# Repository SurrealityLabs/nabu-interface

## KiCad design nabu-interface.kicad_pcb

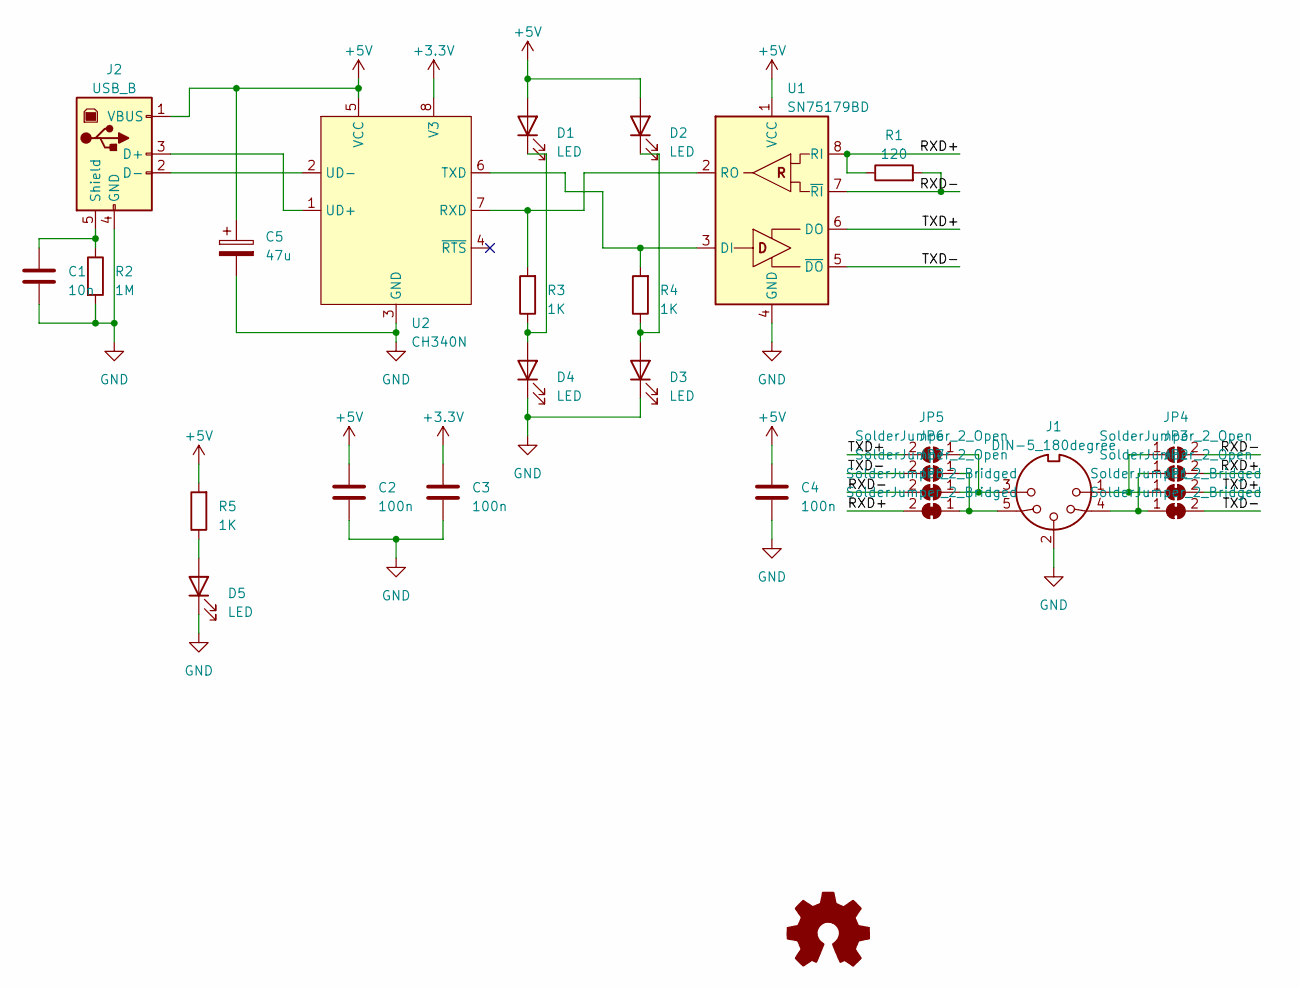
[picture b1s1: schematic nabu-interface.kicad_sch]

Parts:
C1: 10n; C_0603_1608Metric_Pad1.08x0.95mm_HandSolder
C2, C3, C4: 100n; C_0603_1608Metric_Pad1.08x0.95mm_HandSolder
C5: 47u; CP_Radial_D4.0mm_P2.00mm
D1, D2, D3, D4, D5: LED; LED_0603_1608Metric_Pad1.05x0.95mm_HandSolder
J1: DIN-5_180degree; MIDI_DIN5
J2: USB_B; USB_B_OST_USB-B1HSxx_Horizontal
JP1, JP2, JP7, JP8: SolderJumper_2_Bridged; SolderJumper-2_P1.3mm_Bridged_RoundedPad1.0x1.5mm
JP3, JP4, JP5, JP6: SolderJumper_2_Open; SolderJumper-2_P1.3mm_Open_RoundedPad1.0x1.5mm
R1: 120; R_0603_1608Metric_Pad0.98x0.95mm_HandSolder
R2: 1M; R_0603_1608Metric_Pad0.98x0.95mm_HandSolder
R3, R4, R5: 1K; R_0603_1608Metric_Pad0.98x0.95mm_HandSolder
U1: SN75179BD; SOIC-8_3.9x4.9mm_P1.27mm
U2: CH340N; SOP-8_3.9x4.9mm_P1.27mm

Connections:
+3.3V: C3.1, U2.8 (V3)
+5V: C2.1, C4.1, C5.1, D1.2 (A), D2.2 (A), J2.1 (VBUS), R5.2, U1.1 (VCC), U2.5 (VCC)
/RXD+: JP3.2 (B), JP8.2 (B), R1.1, U1.8 (RI)
/RXD-: JP4.2 (B), JP7.2 (B), R1.2, U1.7 (~RI)
/TXD+: JP2.2 (B), JP5.2 (B), U1.6 (DO)
/TXD-: JP1.2 (B), JP6.2 (B), U1.5 (~DO)
GND: C1.2, C2.2, C3.2, C4.2, C5.2, D3.1 (K), D4.1 (K), D5.1 (K), J1.2, J2.4 (GND), R2.2, U1.4 (GND), U2.3 (GND)
unnamed: D1.1 (K), D4.2 (A), R3.1
unnamed: D2.1 (K), D3.2 (A), R4.1
unnamed: D5.2 (A), R5.1
unnamed: J2.3 (D+), U2.1 (UD+)
unnamed: J2.2 (D-), U2.2 (UD-)
unnamed: C1.1, J2.5 (Shield), R2.1
unnamed: J1.4, JP1.1 (A), JP3.1 (A)
unnamed: J1.1, JP2.1 (A), JP4.1 (A)
unnamed: J1.3, JP5.1 (A), JP7.1 (A)
unnamed: J1.5, JP6.1 (A), JP8.1 (A)
unnamed: R4.2, U1.3 (DI), U2.6 (TXD)
unnamed: R3.2, U1.2 (RO), U2.7 (RXD)

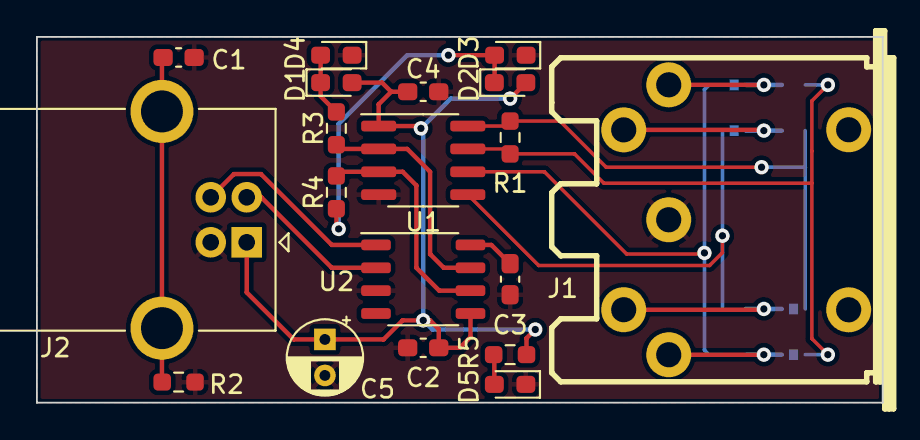
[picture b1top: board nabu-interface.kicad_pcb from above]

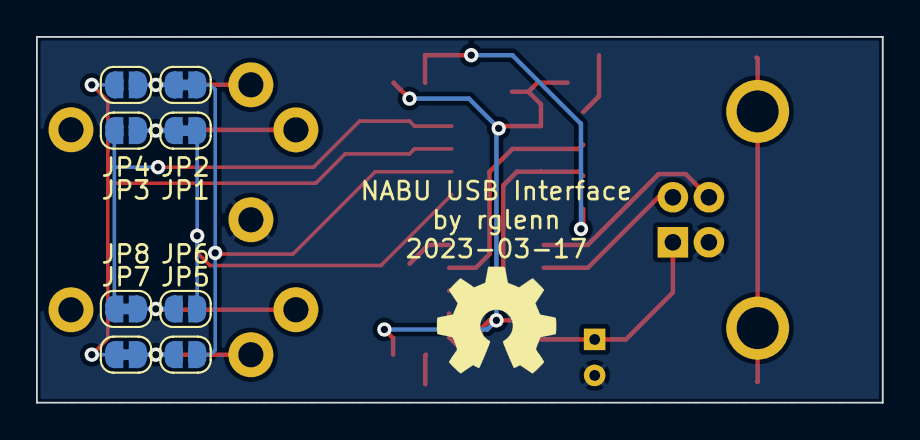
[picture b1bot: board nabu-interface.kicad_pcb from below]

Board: 2 copper layers, 47.0 x 20.3 mm, 27 parts (8 on the bottom side), 19 nets.

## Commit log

2023-03-19 Adding first rev of PCB
